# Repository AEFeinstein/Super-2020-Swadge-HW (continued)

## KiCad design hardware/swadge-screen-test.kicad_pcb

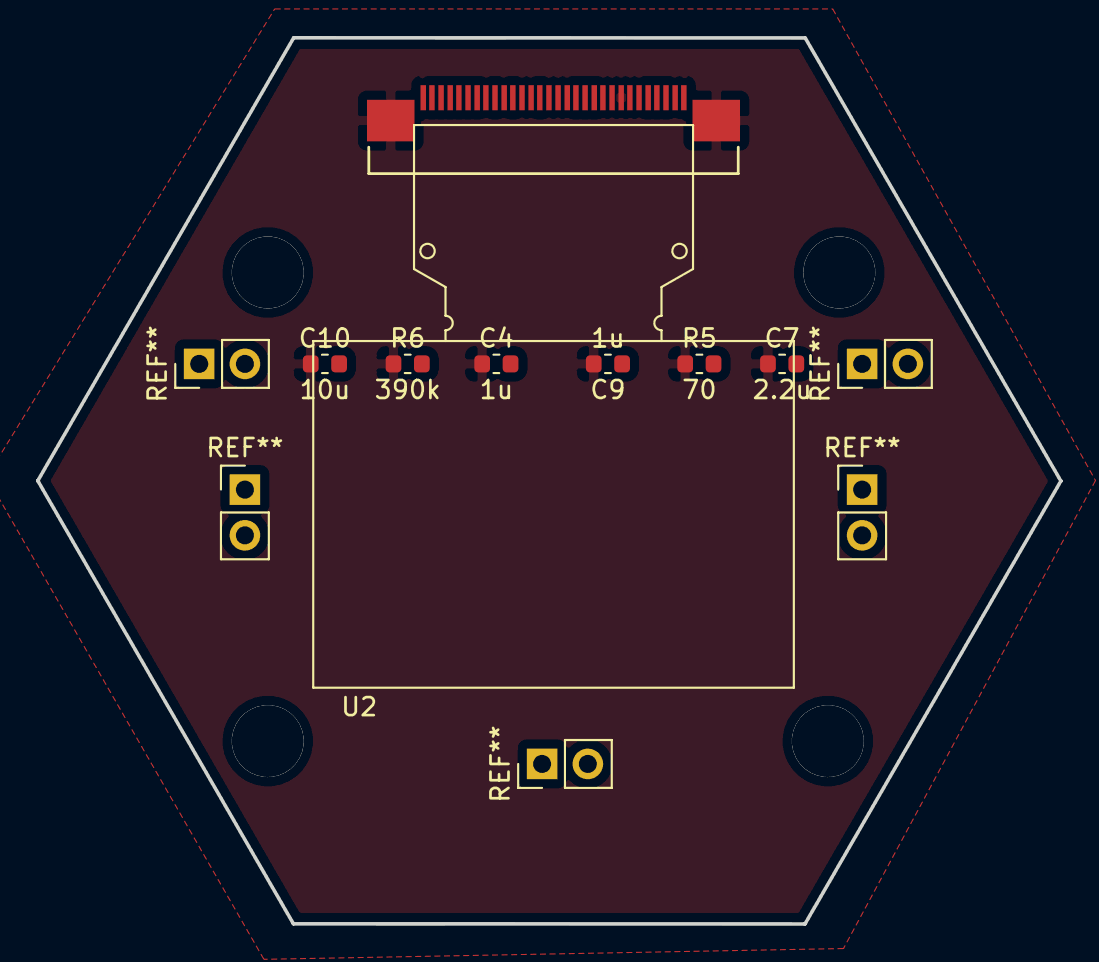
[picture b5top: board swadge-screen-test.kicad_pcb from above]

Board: 2 copper layers, 56.8 x 49.2 mm, 8 parts (1 on the bottom side), 12 nets, no tracks yet.

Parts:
C4, C9: 1u; C_0603_1608Metric
C7: 2.2u; C_0603_1608Metric
C10: 10u; C_0603_1608Metric
R5: 70; R_0603_1608Metric
R6: 390k; C_0603_1608Metric
U2, U2#2: DISP_OLED_UG-2864HSWEG01; oled-flat

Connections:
+3V3: C4.2, U2.6, U2.9, U2.11, U2#2.6, U2#2.9, U2#2.11
GND: C4.1, C7.1, C9.2, C10.1, R5.1, R6.1, U2.1, U2.8, U2.10, U2.12, U2.13, U2.15, U2.16, U2.17, U2.21, U2.22, U2.23, U2.24, U2.25, U2.29, U2.30, U2.31, U2.32, U2#2.1, U2#2.8, U2#2.10, U2#2.12, U2#2.13, U2#2.15, U2#2.16, U2#2.17, U2#2.21, U2#2.22, U2#2.23, U2#2.24, U2#2.25, U2#2.29, U2#2.30, U2#2.31, U2#2.32
unnamed: U2.4, U2#2.4
unnamed: U2.5, U2#2.5
unnamed: C7.2, U2.27, U2#2.27
unnamed: C9.1, U2.2, U2#2.2
unnamed: U2.3, U2#2.3
unnamed: C10.2, U2.28, U2#2.28
unnamed: R6.2, U2.26, U2#2.26
SCL: U2.18, U2#2.18
SDA: U2.19, U2.20, U2#2.19, U2#2.20
_RES: U2.14, U2#2.14

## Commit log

2019-01-12 Added initial project with a single ESP-12F
2019-01-12 Worked on the schematic
    Added accelerometer part lib
2019-01-12 Did a bit of routing
2019-01-13 Added PCIE connector
2019-01-13 Routed everything
2019-01-14 Added I2C display
    Schematic copied from https://github.com/adafruit/Adafruit-1.3inch-128x64-Mono-OLED-PCB
2019-01-14 Better silkscreen & GND plane fill
2019-01-14 Add local library paths, 3D model for ESP
2019-01-14 Updated power switch
2019-01-15 Added WS2812B 3D model. Fixed MMA8452Q 3D model
2019-01-15 Added more 3D parts!
2019-01-16 Made a new microphone footprint, added 3D microphone model
2019-01-17 Replaced MMA8452Q accelerometer with MSA300
2019-01-19 Added second accelerometer, MMA8452Q
2019-01-19 Added programmer schematic and layout
2019-01-19 Added power switches & pin headers to programmer
2019-01-22 Merged libraries, footprints, and 3d shapes
2019-01-22 Started updating programmer to use local parts
2019-01-24 Made board symmetrical wrt. the PCI connector
    Moved batteries to the back, imported Swadge 2019 battery footprint
    Reoriented accelerometers so they match orientation
    Fattened up power traces
2019-01-25 Moved mic away from battery
    Updated DRC to use CNLohr's numbers
2019-01-30 Moved all programmer parts into this repo
    Resized programmer, rerouted programmer, added holes
2019-02-02 Updated library with manufacturing info followiong cnlohr's kicad_for_mfg
    Updated all traces (except accelerometer traces) to 0.0077in
    Replaced microphone with bigger, cheaper one
2019-02-02 Removed NOBOM from parts which didn't need it Added BOM tools
2019-02-02 Updated programmer traces, parts, BOM
2019-02-22 Added SAO Moved mic out of the way of buttons Swapped 1.3" display for 0.96" display Linked vishay display instead of adafruit one
2019-02-23 Added magfest logo & PCB color swatches
2019-02-23 Added SVG files used to make footprints with svg2mod
2019-02-23 Added digikey part numbers for passives Updated PCB color swatch, logo Added name & version to PCB
2019-02-23 Updated digikey part numbers Added graphics to swadge programmer PCB
2019-02-23 Updated digikey part numbers
2019-02-23 Added PCB note Output manufacture files for 1.0.0
2019-03-11 Added digikey part for PCIe connector on the programmer
2019-03-14 Updated digikey part number for 220k resistor
2019-03-15 Updated digikey part for resistors
2019-04-02 #16 replace GPIO switches with buttons in schematic
2019-04-02 #7 Cross RX and TX coming off CP2102n in schematic
2019-04-02 #5 Added FTDI-ordered breakout of all UART pins
2019-04-02 #1 Added silkscreen dot for CP2012n orientation
2019-04-02 #1 #2 #3 #5 #6 #7 #16 Routed PCB
2019-04-02 Swapped RX/TX on FTDI header, added voltage jumper selector
2019-04-04 #11 Remap GPIO, remove extra I2C pullups, remove SPI lines
2019-04-04 #9 Ground extra display pins
2019-04-04 #15 flipped mic pads in footprint
2019-04-04 #12 Upgrades SAO to V1.69BIS
2019-04-04 #14 Replaced ESP-12F with ESP-WROOM-02D
2019-04-04 one more save
2019-04-05 #9 #11 #13 #14 #15 Routed everything
2019-04-06 #17 Reordered PCIe connector for WROOM sanity
2019-04-06 gitignore cleanup
2019-04-07 #17 Reordered PCIe connector on programmer
2019-04-07 #18 Add caps to WROOM power lines
2019-04-07 #12 Swapped USB & Power Switch
2019-04-08 #19 Update AA holder footprints, move them further apart too
2019-04-08 Updated WROOM with digikey p/n. Tweaked layout
2019-04-09 Shortened board
2019-04-10 #4 Add Rubber foot to hole part, update digikey values
2019-04-10 Fix datasheets
2019-04-10 Fix datasheets some more
2019-04-10 Fill polys
2019-05-14 Added Gainsil GS321-TR opamp
2019-05-17 Added QMA6981 accelerometer to the library
2019-05-17 Added back missing battery, PCB art
2019-05-17 Added QMA6981 to the devkit
2019-05-17 Fixed silkscreen
2019-05-28 Added new QMA6981 footprint, no more DRC errors
2019-05-28 Fixed DRC error, silkscreen
2019-06-27 Backlink to CADLAB.io has been added.
2019-07-22 Removed caches from gitignore for cadlab.io
2019-07-22 Added cache.lib files for cadlab.io
2019-08-01 Added model for OLED
2019-08-01 Added 3D model of OLED to board
2019-08-01 Added freecad file for OLED
2019-08-02 Added 3D OLED part with curved connector
2019-08-02 Swapped 3D OLED model for the devkit
2019-08-05 Added banana outline part
2019-08-06 Added banana
2019-08-18 Reworked banana, started laying it out
2019-08-20 Added barrel board
2019-08-20 Rough placement of barrel parts
2019-08-21 Added 12mm buttons
2019-08-21 More barrel layout, more barrel routing
2019-08-21 Added thaeli's swadge-screen-test files
2019-08-21 Added backside of screen-test board
2019-08-21 Made holes bigger
2019-08-21 Added copper pour to the front
2019-08-21 Added buzzer and transistor parts
2019-08-22 Added THT buzzer to barrel board
2019-08-31 Routed board and lots of other things
2019-09-01 Now has a single hole
2019-09-02 fixed all DRC errors
2019-09-02 Moved a lot of silk to F.Fab. Updated buzzer footprint
2019-09-02 Updated ESP model
2019-09-02 Added 0ohm support resistors
2019-09-02 #21 added LED OUT to PCIe connector
2019-09-04 Switched to elecrow FPC part. moved around things. added art, version
2019-09-04 Tweaked manufacturing output
2019-09-07 Replaced 0805 caps with 1206 caps
2019-09-07 Added BOM descriptions:
2019-09-07 Finished BOM notes
2019-09-07 added dummy file for the folder
2019-09-07 Moved barrel into it's own folder
2019-09-07 Moved all projects into separate folders
2019-09-07 added sym-lib-table files
2019-09-07 Updated sym-lib-table files to use relative paths
2019-09-07 Barrel BOM
2019-09-08 Added fp-lib-table files
2019-09-08 Fixed 3D model paths
2019-09-08 Fixed 3D model paths, Updated to version 1.0.1
2019-09-08 Fixed 3d model paths for all projects
2019-09-08 Fixed some bent traces
2019-09-16 #26 Remapped buttons to match devkit gpios
2019-09-16 Flipped OLED contacts, haven't routed them yet #24
2019-09-16 #24 Rerouted OLED traces
2019-09-16 Organized passives
2019-09-18 Added SVG files
2019-09-18 Added headband part and 3D model
2019-09-18 Added project for the headband part
2019-09-23 Reset banana board to a blank slate for cnlohr
2019-09-23 Changed banana OLED to wraparound
2019-09-24 Bump design with some placements.
2019-10-18 Added Magfest logo to headband, in metal
2019-10-19 Added vertical banding, shifted parts to avoid the bands
2019-10-22 Removed transistor from the buzzer circuit. It's louder this way Updated buzzer part info Updated headband part info Adjusted orientation of accelerometer passives
2019-10-23 Added 7 inch banana outline
2019-10-23 bump swadge-banana
2019-10-24 Removed some capacitance from 3.3V, added some capacitance to 5V
2019-10-24 Updated BOM notes
2019-10-24 Incremetned barrel version
2019-10-24 Added manufacturing output in pcb file, ignored manufacturing dir
2019-10-24 Updated descriptions to be more CSV friendly
2019-10-24 Added mfg folder to PCB file, ignored mfg folder
2019-10-24 Bump design
2019-10-24 Updated banana sch/pcb from barrel
2019-10-25 Added funkus & themed logo PCB art files
2019-10-25 Added art to PCB
2019-10-25 Added H2 part designator
2019-10-25 This routing is bananas
2019-10-25 Add cahce.
2019-10-26 Merged cnlohr's changes
2019-10-26 Added power parts to Swadge_Parts library Modified swadge-banana.sch to use new power parts Removed cnlohr specific paths from sym-lib-table
2019-10-26 Modified barrel and programmer to use Swadge_Parts's power parts
2019-10-26 Copied schematic from barrel, again Reimported schematic into layout, fixed capacitor changes Fixed one DRC violation
2019-10-27 Add plots and BOM
2019-10-28 Properly aligned accelerometer Moved C15 closer to accelerometer
2019-10-28 Bump to Rev A with Adam's change
2019-11-01 Changed headband art to a simple square wave
2019-11-01 Made square wave squarer
2019-11-02 Added silk for power switch
2019-11-09 Replaces test text with URL
2019-11-10 Updated & added silkscreen * Buttons * PCIe connector * Version * Tilted MAGFEST logo * Added note that USB is power-only * Website text
2019-11-10 Added & Updated silkscreen * Labeled buttons, power switch * Labeled PCIe connector * Added funkus & logo graphics * Added note that USB is power only * Added instruction URL * Updated revision
2019-11-10 Rotated banana text to be consistent
2019-11-11 Added bananaraptor to swadge-banana
2019-11-11 Added hole Moved R2, embiggened bananaraptor
2019-11-11 Moved R2 back to original position so stencil & pick-n-place won't change Made bananaraptor even bigger
2019-11-11 Readded missing batteries, filled zones
2019-11-12 Added banana label to the back of the banana Rotated Lil'B on the front of the banana
2019-11-12 Tweaking
2019-11-12 Changed I2C pullups to 1K Updated digikey part numbers on BOM
2019-11-12 (Banana this time) Changed I2C pullups to 1K Updated digikey part numbers on BOM
2019-11-12 Made I2C traces to accel less right angly
2019-11-13 cleanup for mfg
2019-11-15 Added series I2C resistors to QMA6981
2019-11-15 Added series I2C resistors to QMA6981 (Banana)
2019-11-16 Removed cnlohr's local paths
2019-11-20 Added new QMA6981 part with larger pads Updated banana and barrel with new pads
2019-11-20 Resized QMA6981_2 pads to 0.3mm x 0.3mm
2019-12-28 Added schematic image
2019-12-31 Fix path for accel 3D object
2020-04-28 Added nav switch
2020-04-30 Added mic part
2020-11-11 Switch to Swadge-Parts for 3D models
2020-11-11 Fix new 3D models
2020-11-12 Use .step models for banana
